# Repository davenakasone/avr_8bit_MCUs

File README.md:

examples for a microcontroller class

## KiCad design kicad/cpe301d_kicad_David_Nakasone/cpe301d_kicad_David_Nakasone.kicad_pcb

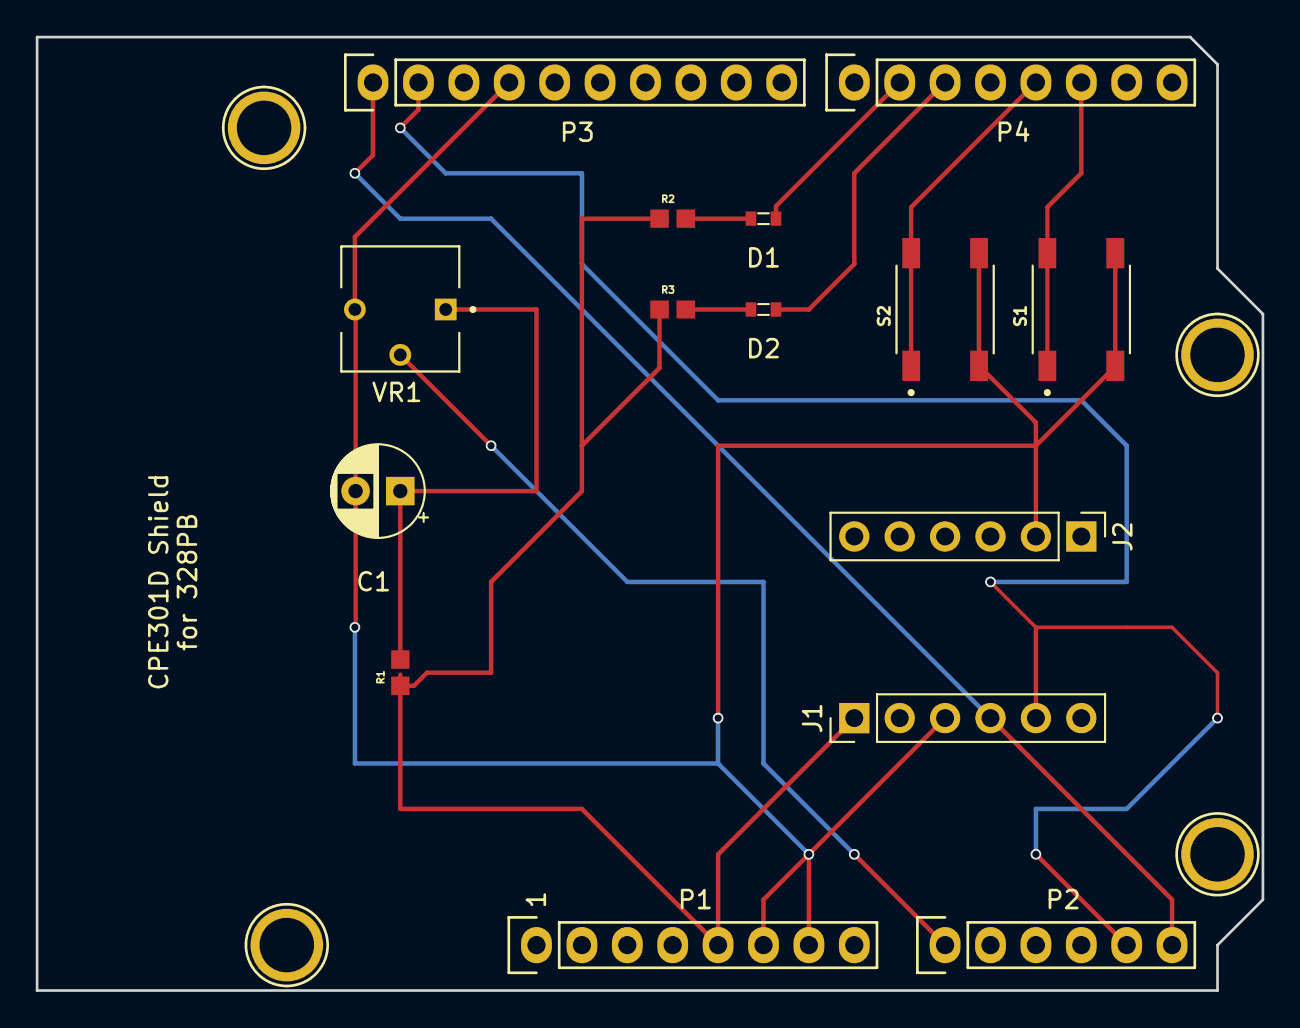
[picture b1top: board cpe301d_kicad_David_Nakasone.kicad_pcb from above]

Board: 2 copper layers, 68.6 x 53.3 mm, 19 parts (0 on the bottom side), 12 nets.

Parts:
C1: 100nF; CP_Radial_D5.0mm_P2.50mm
D1: LED1; 0603
D2: LED2; 0603
J1: J1; PinHeader_1x06_P2.54mm_Vertical
J2: J2; PinHeader_1x06_P2.54mm_Vertical
P1: Power; Socket_Strip_Arduino_1x08
P2: Analog; Socket_Strip_Arduino_1x06
P3: Digital; Socket_Strip_Arduino_1x10
P4: Digital; Socket_Strip_Arduino_1x08
P5, P6, P7, P8: CONN_01X01; Arduino_1pin
R1, R2, R3: RC0603JR-071KL; RESC1607X60N
S1: SW1; SW_8-1437565-1
S2: SW2; SW_8-1437565-1
VR1: 3362P-1-103LF; TRIM_3362P-1-103LF

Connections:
+5V: J1.1, P1.5, R1.1, R2.1, R3.1
/2: P4.6, S1.1, S1.2
/3(**): P4.5, S2.1, S2.2
/5(**): D2.1, P4.3
/6(**): D1.1, P4.2
/A0: P2.1, VR1.2
/A4(SDA): J1.5, P2.5, P3.2
/A5(SCL): J1.4, P2.6, P3.1
GND: C1.2, J1.3, J2.2, P1.6, P1.7, P3.4, S1.3, S1.4, S2.3, S2.4, VR1.3
unnamed: C1.1, R1.2, VR1.1
unnamed: D1.2, R2.2
unnamed: D2.2, R3.2

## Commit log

2022-01-18 added demo template
2022-01-18 more
2022-01-18 restructure
2022-01-27 sand box area
2022-01-29 lab work being added, also keeping examples
2022-01-30 more lab
2022-02-01 labs
2022-02-03 da1 initial files
2022-02-04 all designs working, just need report
2022-02-04 forced
2022-02-05 added
2022-02-06 lab2 is good
2022-02-20 lab3/4 added
2022-02-21 DA2 working, just need fritz
2022-02-21 just need fritz?
2022-02-28 files added
2022-02-28 added kikad
2022-03-05 lab work
2022-03-05 lab6 complete
2022-03-07 da3 complete
2022-03-19 midterm
2022-03-26 adding files
2022-03-26 video
2022-04-02 lab9
2022-04-05 midterm 2 is done
2022-04-05 good
2022-04-09 adding lab10
2022-04-09 lab10 complete
2022-04-09 da5 complete
2022-05-02 last labs
2022-05-02 da6 complete
2022-05-02 report
2022-05-08 project files
2022-05-08 kicad is complete, all CPE301/D, CPE301L tasks are complete, turned-in on time, and should be perfect.
